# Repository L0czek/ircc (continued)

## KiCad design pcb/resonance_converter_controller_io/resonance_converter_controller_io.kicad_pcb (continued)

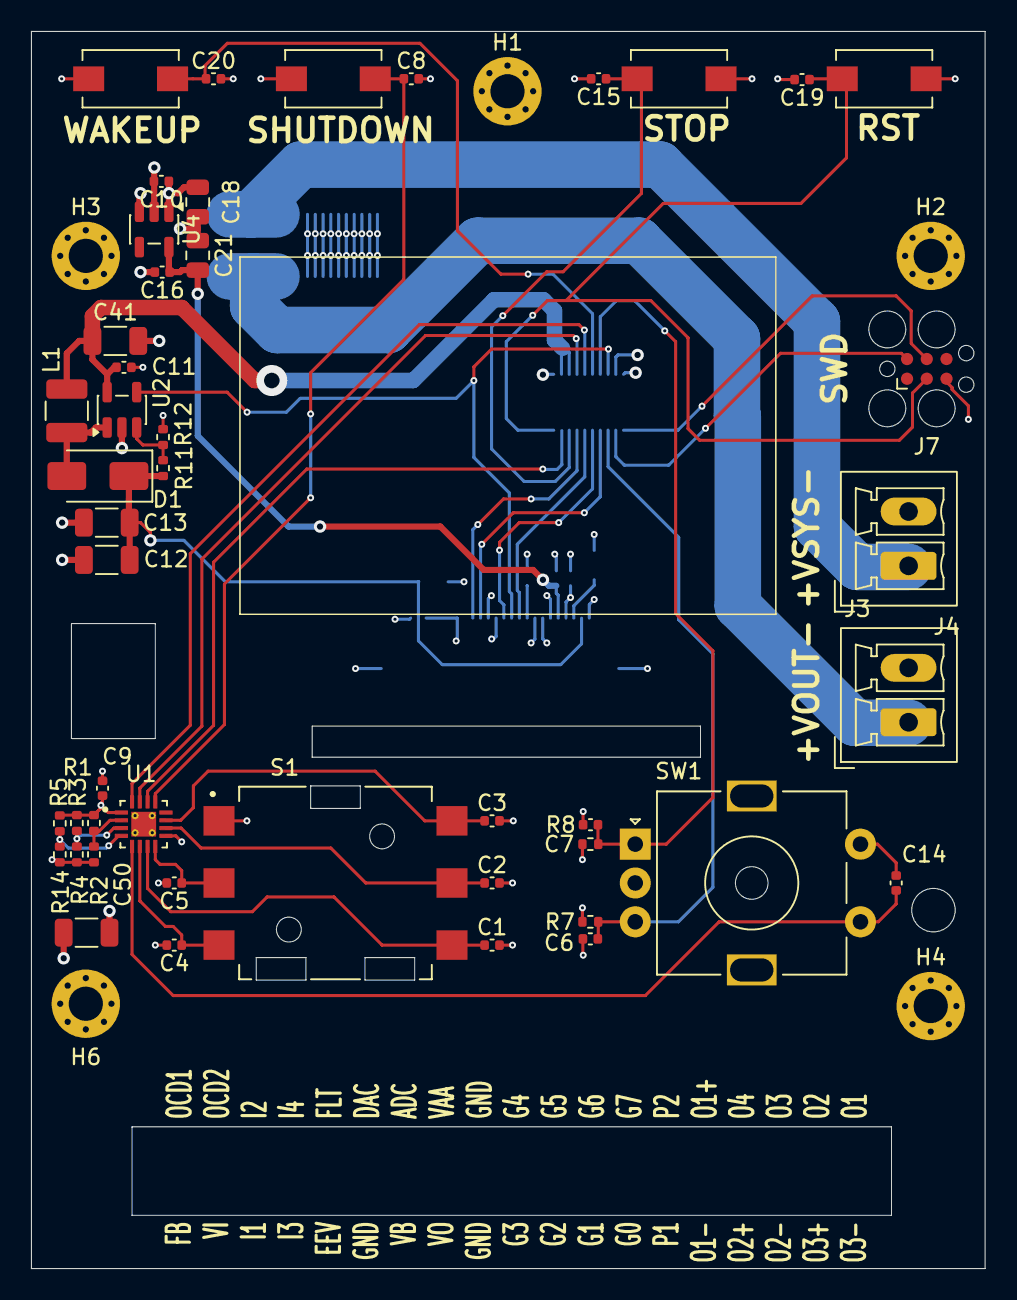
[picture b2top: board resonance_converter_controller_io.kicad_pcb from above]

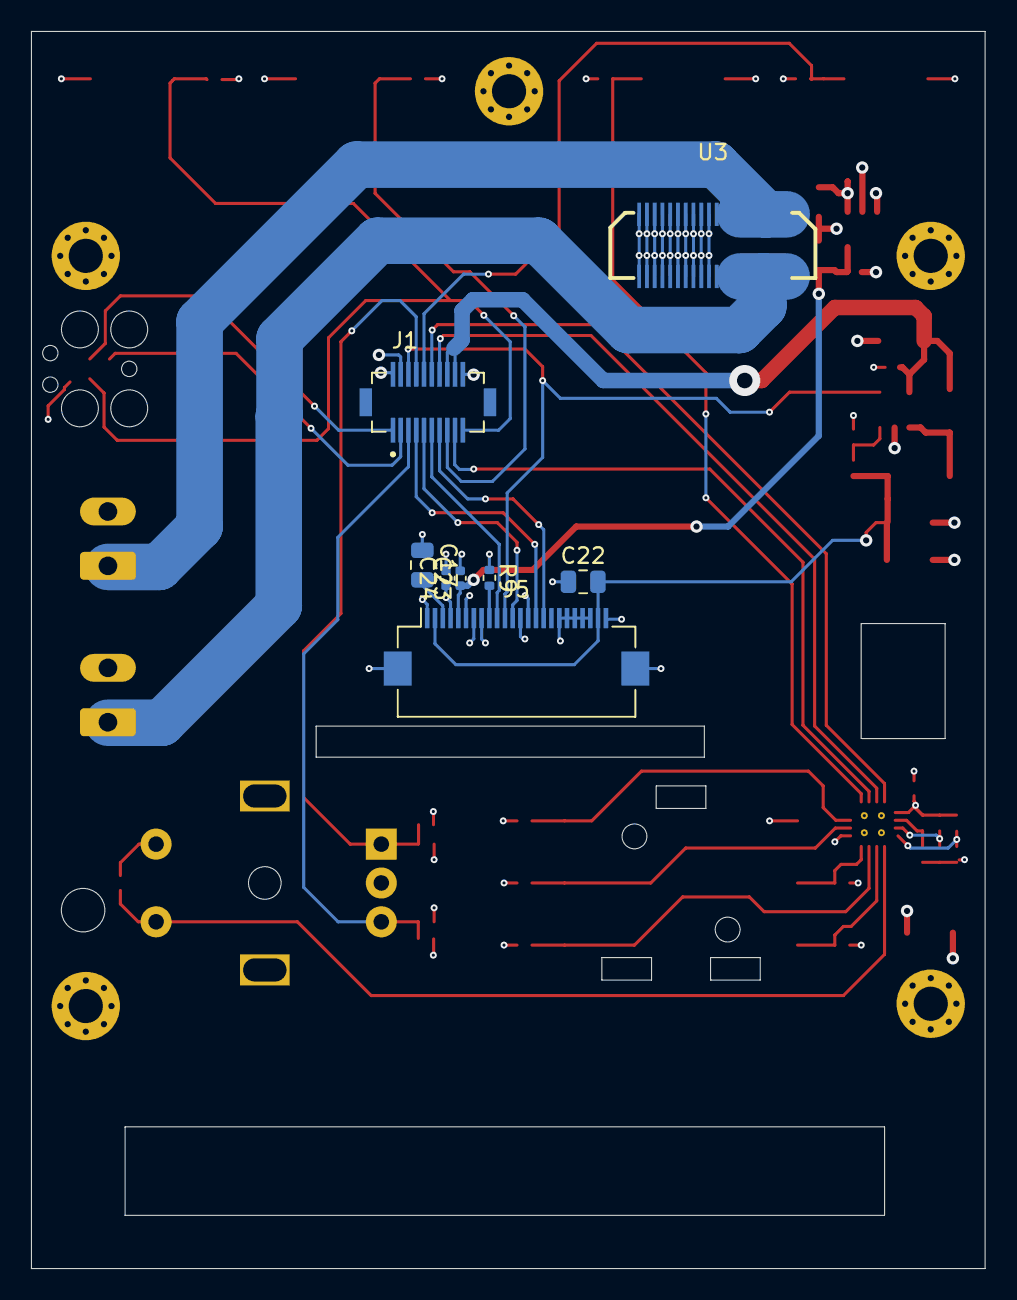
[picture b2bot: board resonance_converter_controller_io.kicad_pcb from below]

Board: 4 copper layers, 61.4 x 79.6 mm, 59 parts (8 on the bottom side), 36 nets.

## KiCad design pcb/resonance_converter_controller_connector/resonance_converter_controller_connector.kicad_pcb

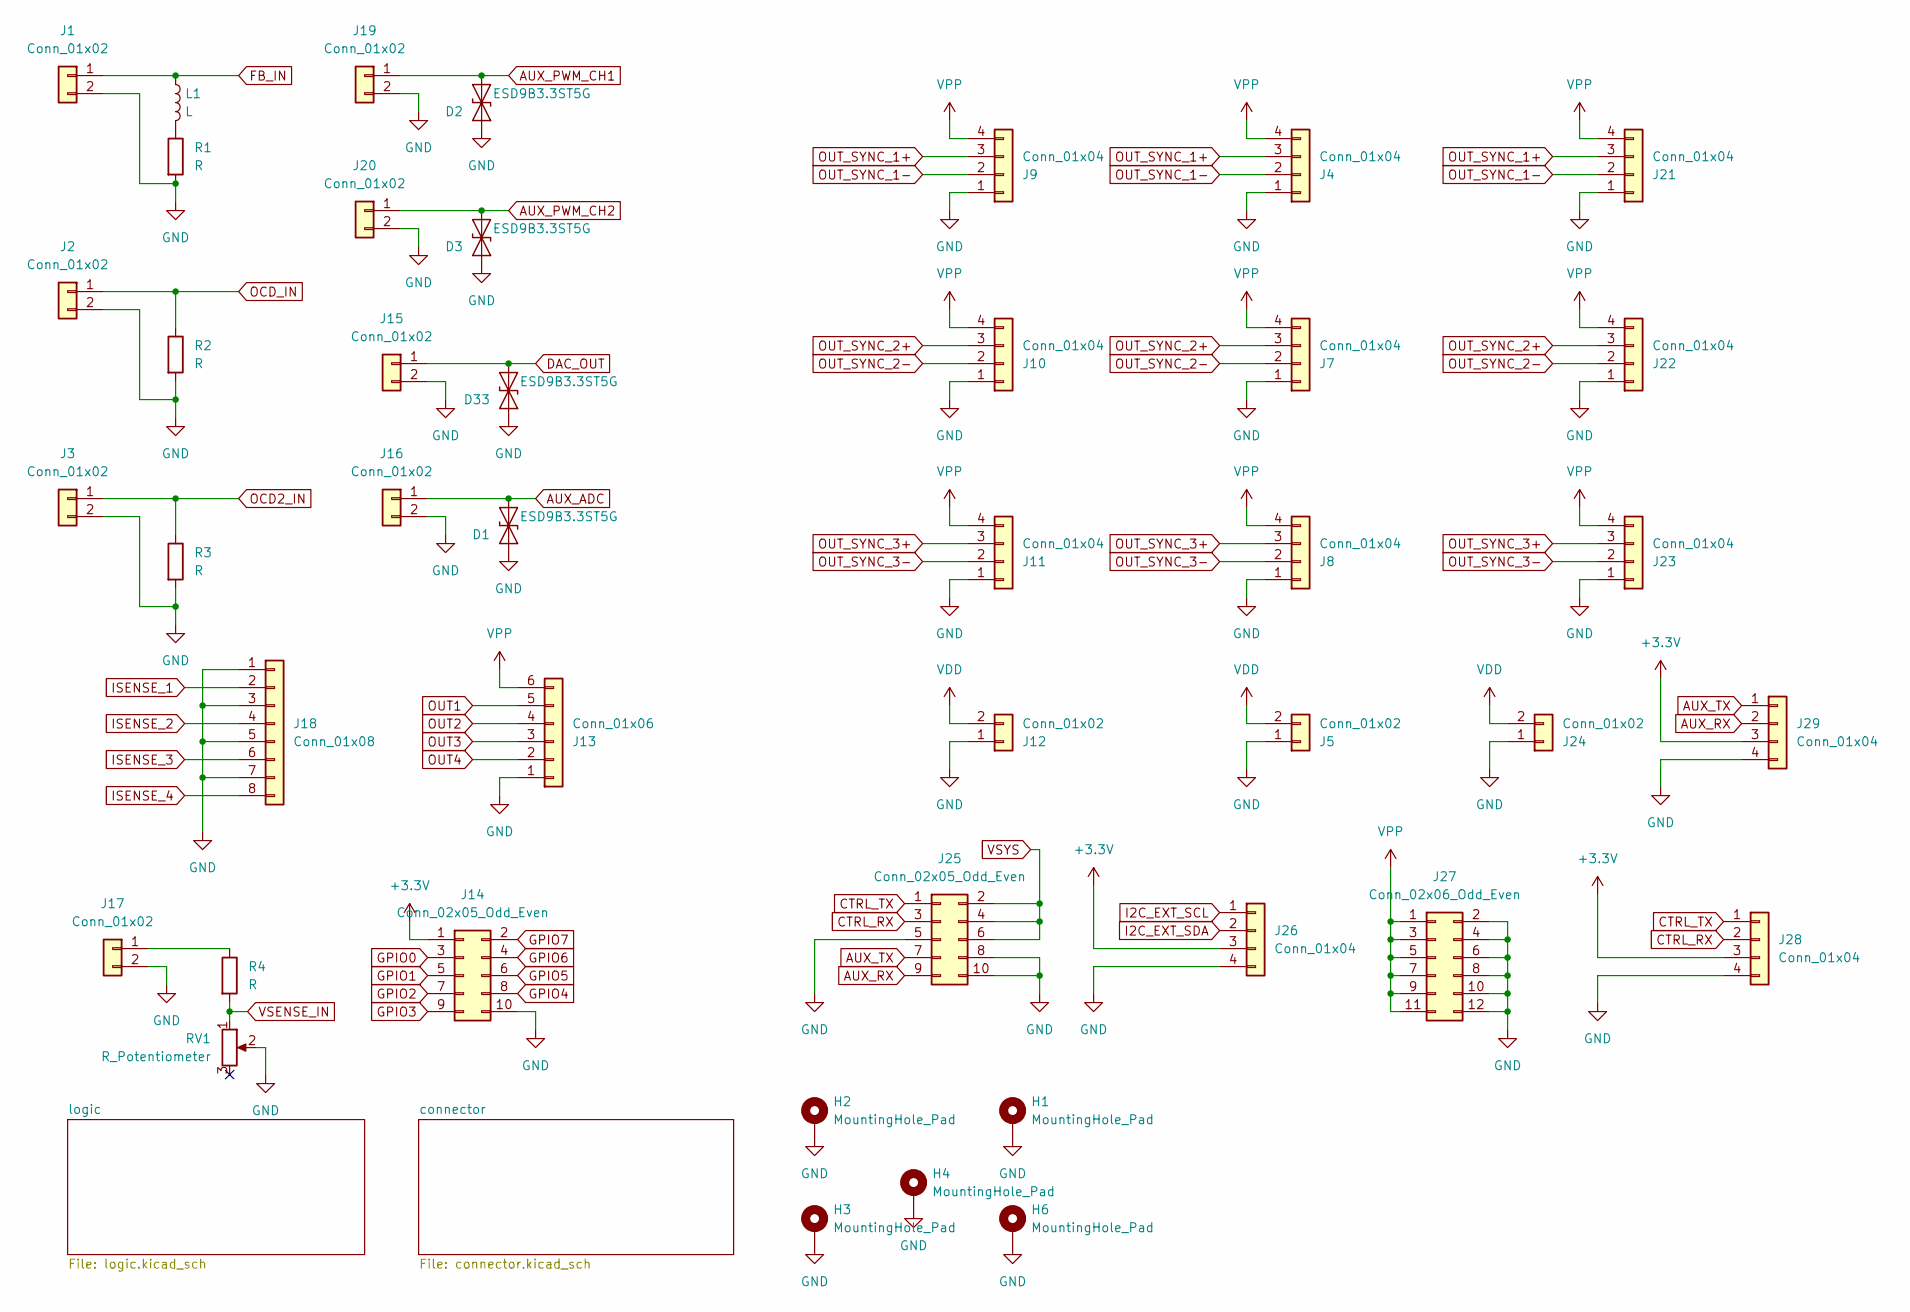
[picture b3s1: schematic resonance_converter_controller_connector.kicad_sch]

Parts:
D1, D2, D3, D33: ESD9B3.3ST5G; D_SOD-923
H1, H2, H3, H4, H6: MountingHole_Pad; MountingHole_2.2mm_M2_Pad_Via
J1, J2, J3, J15, J16, J17, J19, J20: Conn_01x02; PhoenixContact_MCV_1,5_2-G-5.08_1x02_P5.08mm_Vertical
J4, J7, J8, J9, J10, J11, J21, J22, J23, J26, J28, J29: Conn_01x04; JST_PH_B4B-PH-K_1x04_P2.00mm_Vertical
J5, J12, J24: Conn_01x02; AMASS_XT30U-M_1x02_P5.0mm_Vertical
J13: Conn_01x06; JST_PH_B6B-PH-K_1x06_P2.00mm_Vertical
J14, J25: Conn_02x05_Odd_Even; PinHeader_2x05_P2.54mm_Vertical
J18: Conn_01x08; PhoenixContact_MCV_1,5_8-G-3.5_1x08_P3.50mm_Vertical
J27: Conn_02x06_Odd_Even; PinHeader_2x06_P2.54mm_Vertical
L1: L; L_Radial_D12.0mm_P10.00mm_Neosid_SD12_style1
R1, R2, R3: R; TO-220-2_Vertical
R4: R; R_2010_5025Metric
RV1: R_Potentiometer; Potentiometer_Bourns_3269W_Vertical

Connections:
+3.3V: J14.1, J26.3, J28.3, J29.3; also elsewhere on the board
AUX_ADC: D1.1 (A1), J16.1; also elsewhere on the board
AUX_PWM_CH1: D2.1 (A1), J19.1; also elsewhere on the board
AUX_PWM_CH2: D3.1 (A1), J20.1; also elsewhere on the board
AUX_RX: J25.9, J29.2; also elsewhere on the board
AUX_TX: J25.7, J29.1; also elsewhere on the board
CTRL_RX: J25.3, J28.2; also elsewhere on the board
CTRL_TX: J25.1, J28.1; also elsewhere on the board
DAC_OUT: D33.1 (A1), J15.1; also elsewhere on the board
FB_IN: J1.1, L1.1; also elsewhere on the board
GND: D1.2 (A2), D2.2 (A2), D3.2 (A2), D33.2 (A2), H1.1 (1_1), H2.1 (1_1), H3.1 (1_1), H4.1 (1_1), H6.1 (1_1), J1.2, J2.2, J3.2, J4.1, J5.1, J7.1, J8.1, J9.1, J10.1, J11.1, J12.1, J13.1, J14.10, J15.2, J16.2, J17.2, J18.1, J18.3, J18.5, J18.7, J19.2, J20.2, J21.1, J22.1, J23.1, J24.1, J25.5, J25.8, J25.10, J26.4, J27.2, J27.4, J27.6, J27.8, J27.10, J27.12, J28.4, J29.4, R1.2, R2.2, R3.2, RV1.2; also elsewhere on the board
GPIO0: J14.3; also elsewhere on the board
GPIO1: J14.5; also elsewhere on the board
GPIO2: J14.7; also elsewhere on the board
GPIO3: J14.9; also elsewhere on the board
GPIO4: J14.8; also elsewhere on the board
GPIO5: J14.6; also elsewhere on the board
GPIO6: J14.4; also elsewhere on the board
GPIO7: J14.2; also elsewhere on the board
I2C_EXT_SCL: J26.1; also elsewhere on the board
I2C_EXT_SDA: J26.2; also elsewhere on the board
ISENSE_1: J18.2; also elsewhere on the board
ISENSE_2: J18.4; also elsewhere on the board
ISENSE_3: J18.6; also elsewhere on the board
ISENSE_4: J18.8; also elsewhere on the board
unnamed: J17.1, R4.1
unnamed: L1.2, R1.1
OCD2_IN: J3.1, R3.1; also elsewhere on the board
OCD_IN: J2.1, R2.1; also elsewhere on the board
OUT1: J13.5; also elsewhere on the board
OUT2: J13.4; also elsewhere on the board
OUT3: J13.3; also elsewhere on the board
OUT4: J13.2; also elsewhere on the board
OUT_SYNC_1+: J4.3, J9.3, J21.3; also elsewhere on the board
OUT_SYNC_1-: J4.2, J9.2, J21.2; also elsewhere on the board
OUT_SYNC_2+: J7.3, J10.3, J22.3; also elsewhere on the board
OUT_SYNC_2-: J7.2, J10.2, J22.2; also elsewhere on the board
OUT_SYNC_3+: J8.3, J11.3, J23.3; also elsewhere on the board
OUT_SYNC_3-: J8.2, J11.2, J23.2; also elsewhere on the board
VDD: J5.2, J12.2, J24.2; also elsewhere on the board
VPP: J4.4, J7.4, J8.4, J9.4, J10.4, J11.4, J13.6, J21.4, J22.4, J23.4, J27.1, J27.3, J27.5, J27.7, J27.9, J27.11; also elsewhere on the board
VSENSE_IN: R4.2, RV1.1; also elsewhere on the board
VSYS: J25.2, J25.4, J25.6; also elsewhere on the board

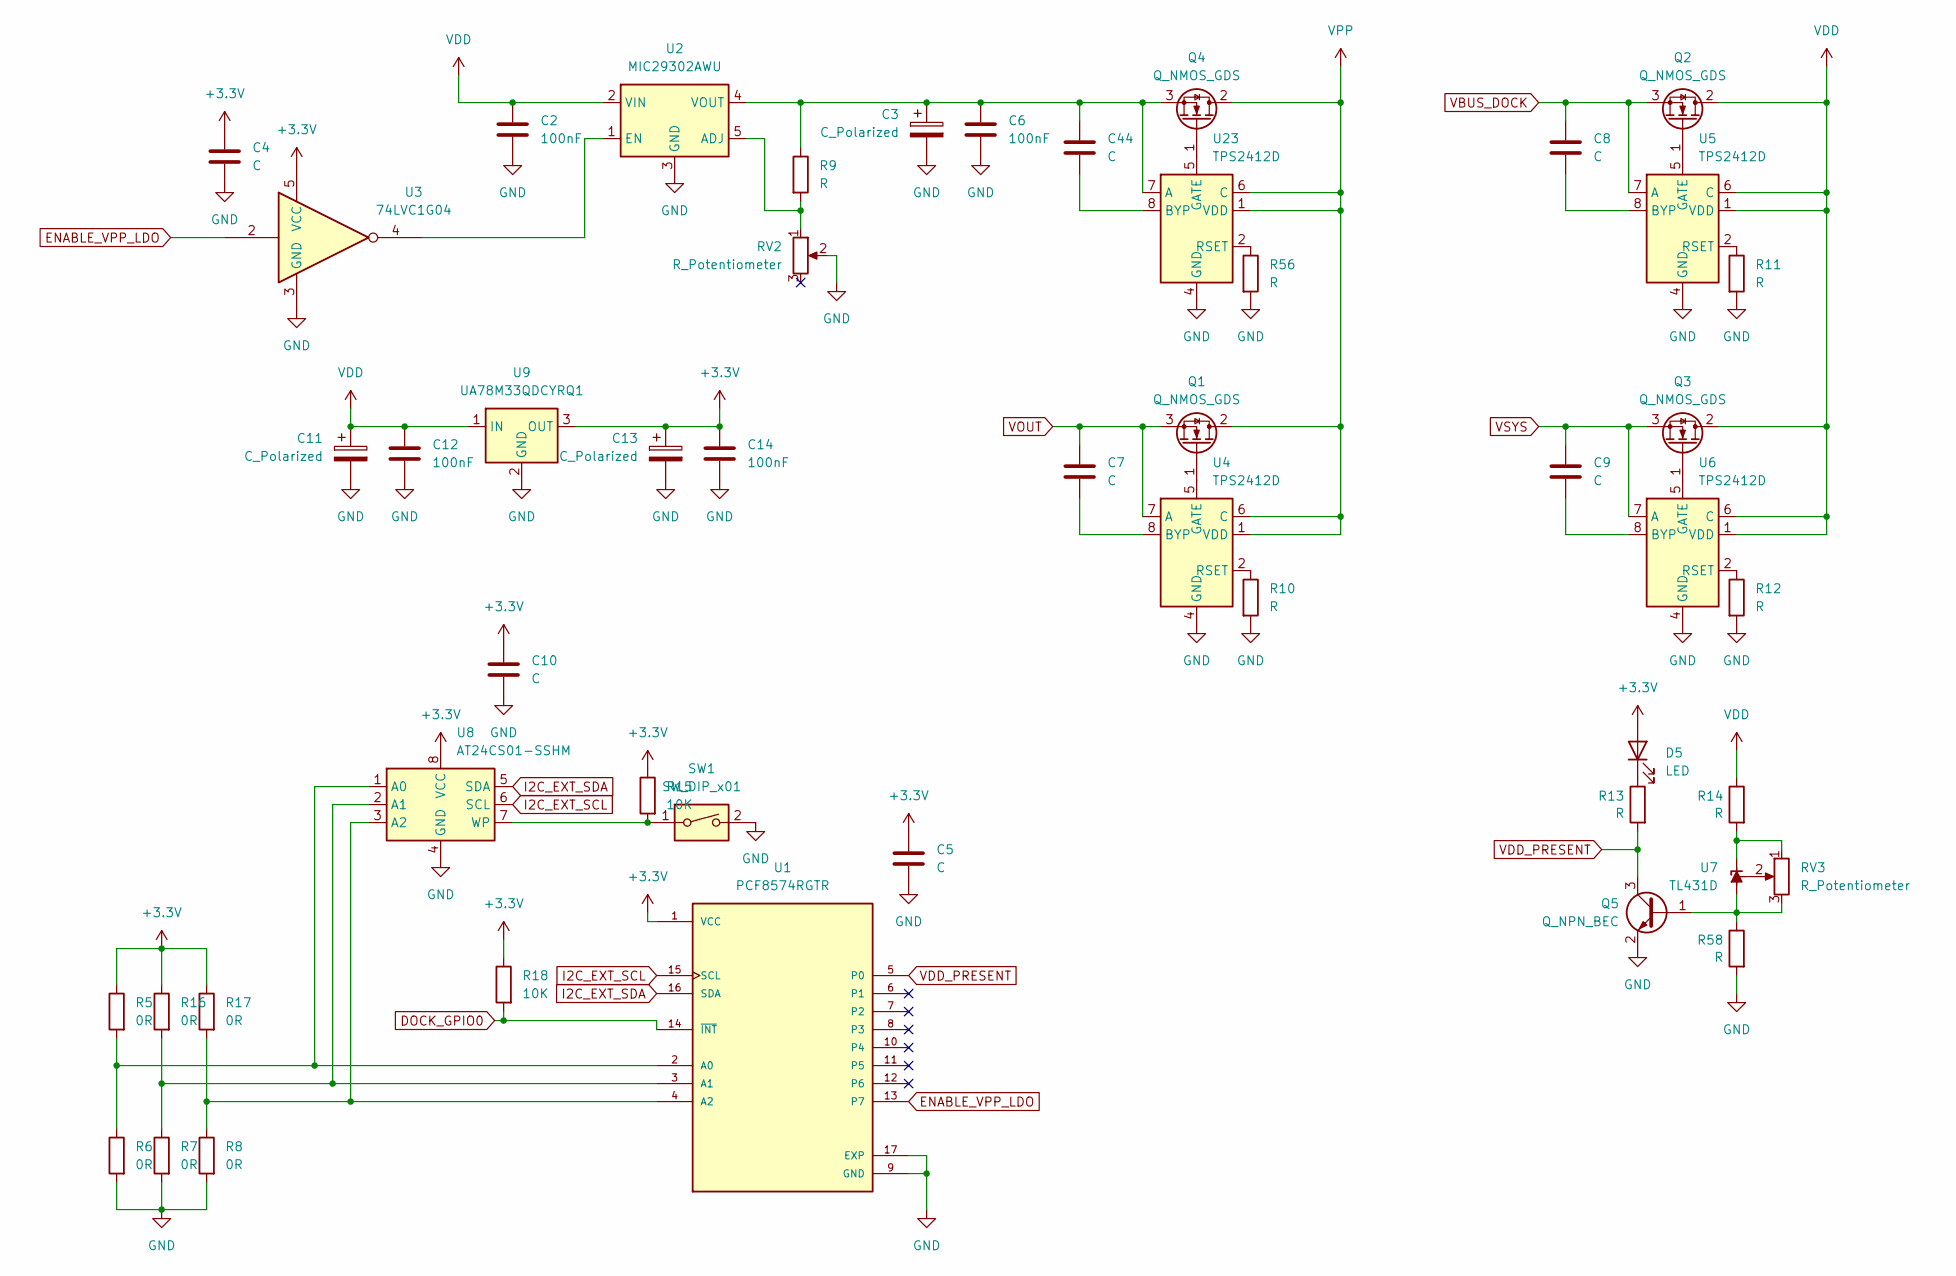
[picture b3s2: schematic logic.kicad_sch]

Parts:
C2, C6, C12, C14: 100nF; C_0402_1005Metric
C3, C11, C13: C_Polarized; CP_Elec_10x10
C4, C5, C7, C8, C9, C10, C44: C; C_0402_1005Metric
D5: LED; LED_1206_3216Metric
Q1, Q2, Q3, Q4: Q_NMOS_GDS; TO-252-2
Q5: Q_NPN_BEC; SOT-23
R5, R6, R7, R8, R16, R17: 0R; R_0402_1005Metric
R9, R10, R11, R12, R13, R14, R56, R58: R; R_0402_1005Metric
R15, R18: 10K; R_0402_1005Metric
RV2, RV3: R_Potentiometer; Potentiometer_Bourns_3269W_Vertical
SW1: SW_DIP_x01; SW_DIP_SPSTx01_Slide_9.78x4.72mm_W8.61mm_P2.54mm
U1: PCF8574RGTR; QFN50P300X300X100-17N; PARTREV J; DigiKey_Part_Number 296-21238-1-ND
U2: MIC29302AWU; TO-263-5_TabPin3
U3: 74LVC1G04; SOT-23-5
U4, U5, U6, U23: TPS2412D; TSSOP-8_4.4x3mm_P0.65mm
U7: TL431D; SOIC-8_3.9x4.9mm_P1.27mm
U8: AT24CS01-SSHM; SOIC-8_3.9x4.9mm_P1.27mm
U9: UA78M33QDCYRQ1; SOT-223-3_TabPin2

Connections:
+3.3V: C4.1, C5.1, C10.1, C13.1, C14.1, D5.2 (A), R5.1, R15.1, R16.1, R17.1, R18.1, U1.1 (VCC), U3.5 (VCC), U8.8 (VCC), U9.3 (OUT); also elsewhere on the board
DOCK_GPIO0: R18.2, U1.14 (~INT)
ENABLE_VPP_LDO: U1.13 (P7), U3.2
GND: C2.2, C3.2, C4.2, C5.2, C6.2, C10.2, C11.2, C12.2, C13.2, C14.2, Q5.2 (E), R6.2, R7.2, R8.2, R10.2, R11.2, R12.2, R56.2, R58.2, RV2.2, SW1.2, U1.9 (GND), U1.17 (EXP), U2.3 (GND), U3.3 (GND), U4.3 (GND), U4.4 (GND), U5.3 (GND), U5.4 (GND), U6.3 (GND), U6.4 (GND), U8.4 (GND), U9.2 (GND), U23.3 (GND), U23.4 (GND); also elsewhere on the board
I2C_EXT_SCL: U1.15 (SCL), U8.6 (SCL); also elsewhere on the board
I2C_EXT_SDA: U1.16 (SDA), U8.5 (SDA); also elsewhere on the board
unnamed: D5.1 (K), R13.1
unnamed: Q1.1 (G), U4.5 (GATE)
unnamed: Q2.1 (G), U5.5 (GATE)
unnamed: Q3.1 (G), U6.5 (GATE)
unnamed: Q4.1 (G), U23.5 (GATE)
unnamed: C3.1, C6.1, C44.1, Q4.3 (S), R9.1, U2.4 (VOUT), U23.7 (A)
unnamed: Q5.1 (B), R58.1, RV3.3, U7.2 (A), U7.3 (A), U7.6 (A), U7.7 (A)
unnamed: R5.2, R6.1, U1.2 (A0), U8.1 (A0)
unnamed: R7.1, R16.2, U1.3 (A1), U8.2 (A1)
unnamed: R8.1, R17.2, U1.4 (A2), U8.3 (A2)
unnamed: R9.2, RV2.1, U2.5 (ADJ)
unnamed: U2.1 (EN), U3.4
unnamed: C7.2, U4.8 (BYP)
unnamed: R10.1, U4.2 (RSET)
unnamed: C8.2, U5.8 (BYP)
unnamed: R11.1, U5.2 (RSET)
unnamed: C9.2, U6.8 (BYP)
unnamed: R12.1, U6.2 (RSET)
unnamed: R14.2, RV3.1, U7.1 (K)
unnamed: RV3.2, U7.8 (REF)
unnamed: R15.2, SW1.1, U8.7 (WP)
unnamed: C44.2, U23.8 (BYP)
unnamed: R56.1, U23.2 (RSET)
VBUS_DOCK: C8.1, Q2.3 (S), U5.7 (A); also elsewhere on the board
VDD: C2.1, C11.1, C12.1, Q2.2 (D), Q3.2 (D), R14.1, U2.2 (VIN), U5.1 (VDD), U5.6 (C), U6.1 (VDD), U6.6 (C), U9.1 (IN); also elsewhere on the board
VDD_PRESENT: Q5.3 (C), R13.2, U1.5 (P0)
VOUT: C7.1, Q1.3 (S), U4.7 (A); also elsewhere on the board
VPP: Q1.2 (D), Q4.2 (D), U4.1 (VDD), U4.6 (C), U23.1 (VDD), U23.6 (C); also elsewhere on the board
VSYS: C9.1, Q3.3 (S), U6.7 (A); also elsewhere on the board

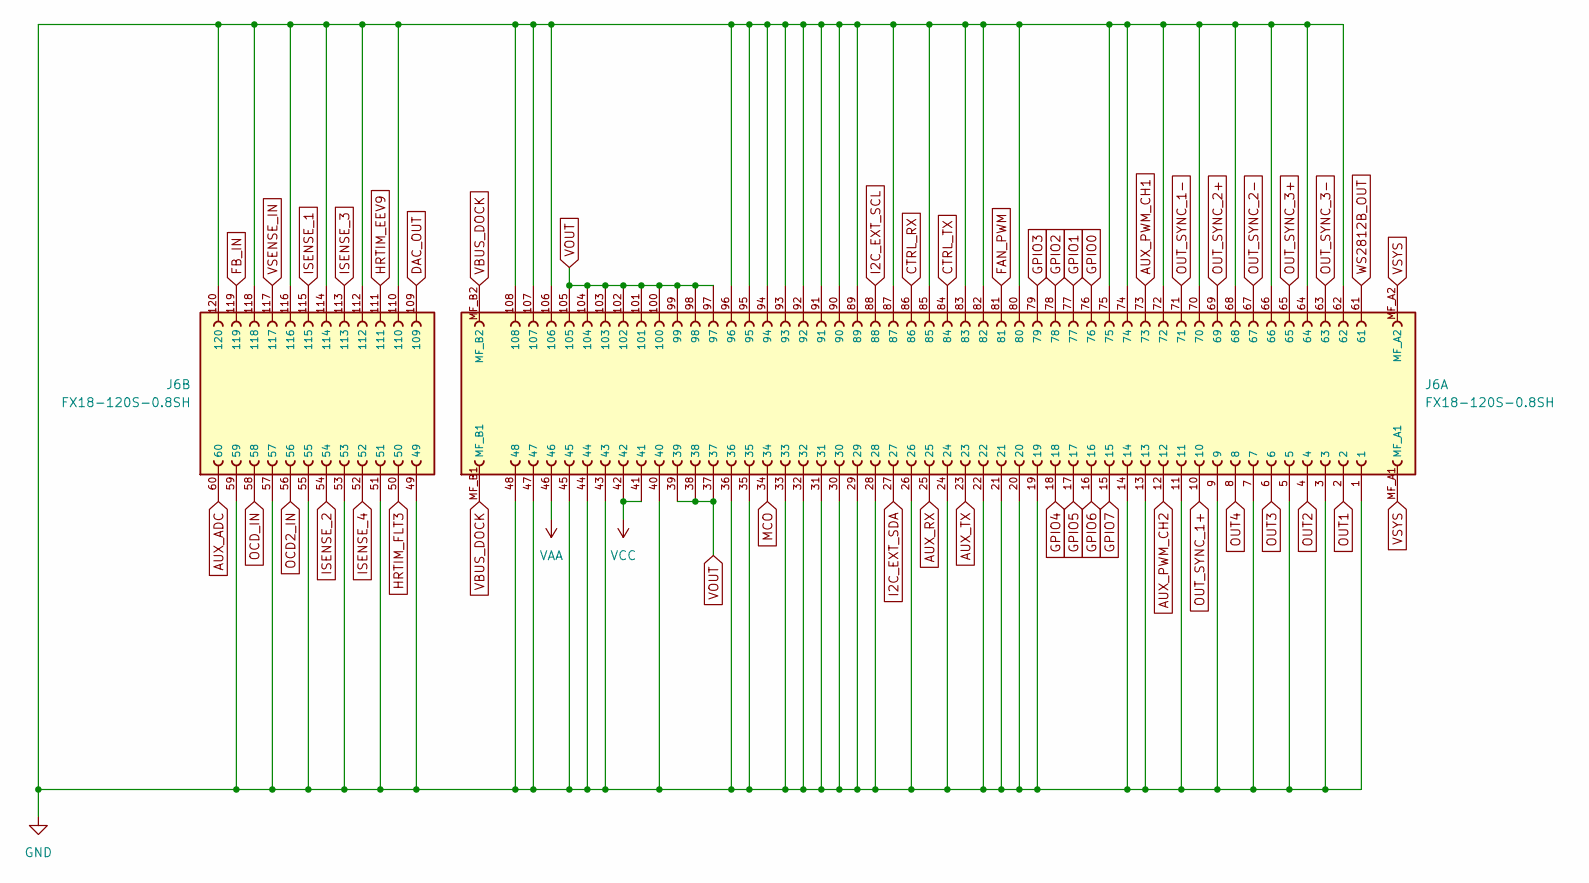
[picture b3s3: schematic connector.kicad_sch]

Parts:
J6: FX18-120S-0.8SH; HIROSE_FX18-120S-0.8SH; PARTREV 1

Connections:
AUX_ADC: J6.60; also elsewhere on the board
AUX_PWM_CH1: J6.73; also elsewhere on the board
AUX_PWM_CH2: J6.12; also elsewhere on the board
AUX_RX: J6.25; also elsewhere on the board
AUX_TX: J6.23; also elsewhere on the board
CTRL_RX: J6.86; also elsewhere on the board
CTRL_TX: J6.84; also elsewhere on the board
DAC_OUT: J6.109; also elsewhere on the board
FAN_PWM: J6.81
FB_IN: J6.119; also elsewhere on the board
GND: J6.1, J6.3, J6.5, J6.7, J6.9, J6.11, J6.13, J6.14, J6.19, J6.20, J6.21, J6.22, J6.24, J6.26, J6.28, J6.29, J6.30, J6.31, J6.32, J6.33, J6.35, J6.36, J6.40, J6.43, J6.44, J6.45, J6.47, J6.48, J6.49, J6.51, J6.53, J6.55, J6.57, J6.59, J6.62, J6.64, J6.66, J6.68, J6.70, J6.72, J6.74, J6.75, J6.80, J6.82, J6.83, J6.85, J6.87, J6.89, J6.90, J6.91, J6.92, J6.93, J6.94, J6.95, J6.96, J6.106, J6.107, J6.108, J6.110, J6.112, J6.114, J6.116, J6.118, J6.120; also elsewhere on the board
GPIO0: J6.76; also elsewhere on the board
GPIO1: J6.77; also elsewhere on the board
GPIO2: J6.78; also elsewhere on the board
GPIO3: J6.79; also elsewhere on the board
GPIO4: J6.18; also elsewhere on the board
GPIO5: J6.17; also elsewhere on the board
GPIO6: J6.16; also elsewhere on the board
GPIO7: J6.15; also elsewhere on the board
HRTIM_EEV9: J6.111
HRTIM_FLT3: J6.50
I2C_EXT_SCL: J6.88; also elsewhere on the board
I2C_EXT_SDA: J6.27; also elsewhere on the board
ISENSE_1: J6.115; also elsewhere on the board
ISENSE_2: J6.54; also elsewhere on the board
ISENSE_3: J6.113; also elsewhere on the board
ISENSE_4: J6.52; also elsewhere on the board
MCO: J6.34
OCD2_IN: J6.56; also elsewhere on the board
OCD_IN: J6.58; also elsewhere on the board
OUT1: J6.2; also elsewhere on the board
OUT2: J6.4; also elsewhere on the board
OUT3: J6.6; also elsewhere on the board
OUT4: J6.8; also elsewhere on the board
OUT_SYNC_1+: J6.10; also elsewhere on the board
OUT_SYNC_1-: J6.71; also elsewhere on the board
OUT_SYNC_2+: J6.69; also elsewhere on the board
OUT_SYNC_2-: J6.67; also elsewhere on the board
OUT_SYNC_3+: J6.65; also elsewhere on the board
OUT_SYNC_3-: J6.63; also elsewhere on the board
VAA: J6.46
VBUS_DOCK: J6.MF_B1, J6.MF_B2; also elsewhere on the board
VCC: J6.41, J6.42
VOUT: J6.37, J6.38, J6.39, J6.97, J6.98, J6.99, J6.100, J6.101, J6.102, J6.103, J6.104, J6.105; also elsewhere on the board
VSENSE_IN: J6.117; also elsewhere on the board
VSYS: J6.MF_A1, J6.MF_A2; also elsewhere on the board
WS2812B_OUT: J6.61

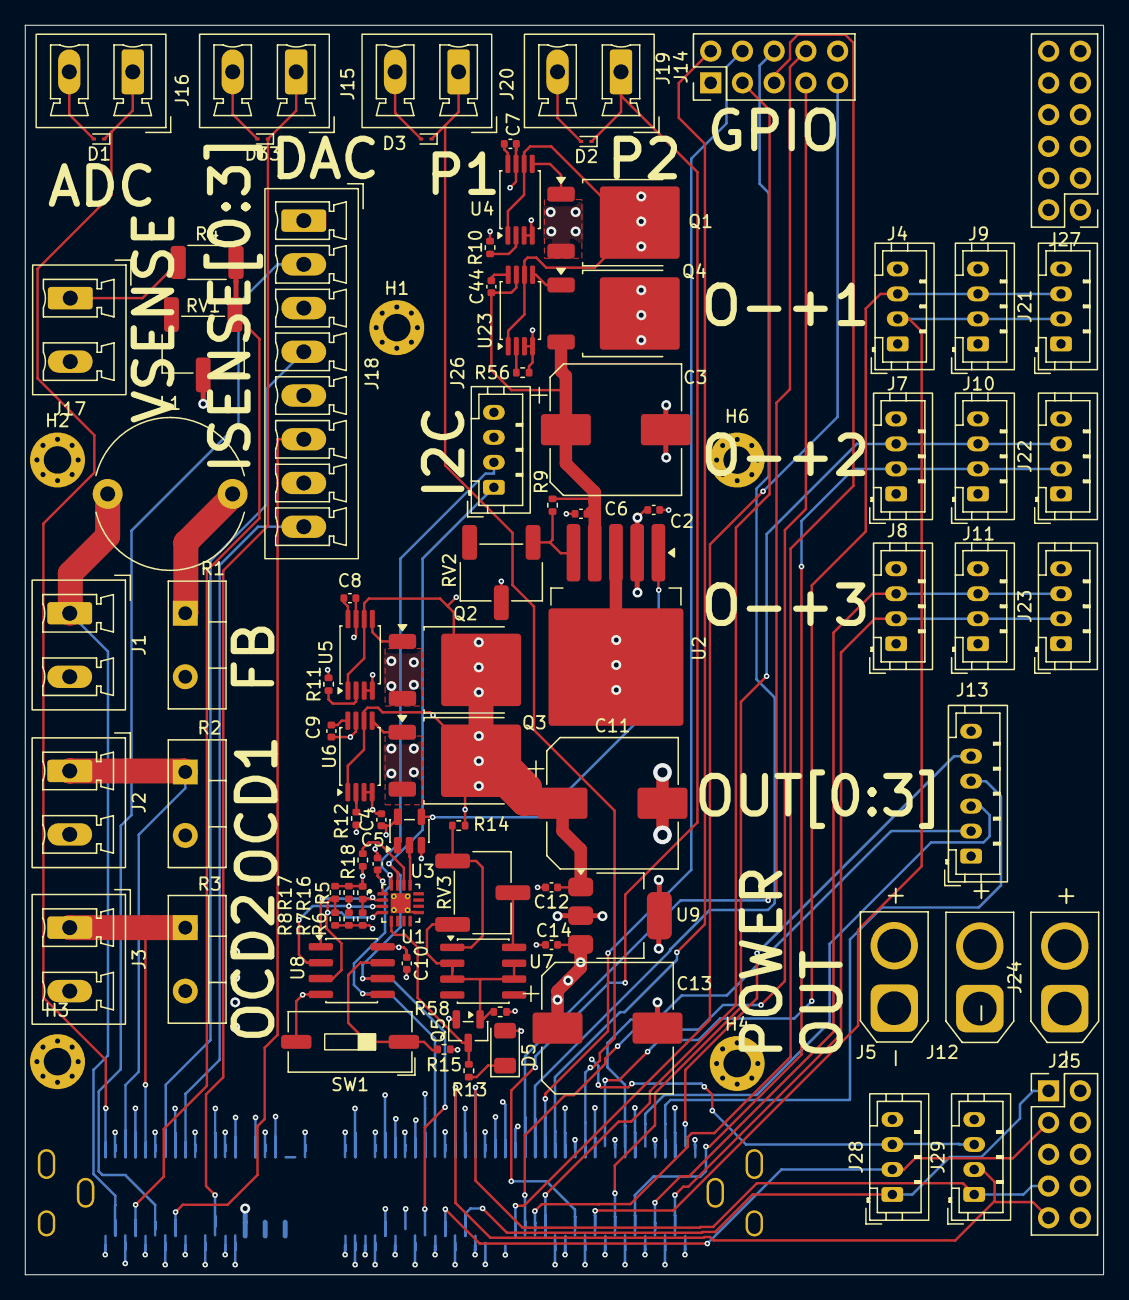
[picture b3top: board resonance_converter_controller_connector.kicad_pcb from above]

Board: 4 copper layers, 86.3 x 100.0 mm, 93 parts (1 on the bottom side), 72 nets.

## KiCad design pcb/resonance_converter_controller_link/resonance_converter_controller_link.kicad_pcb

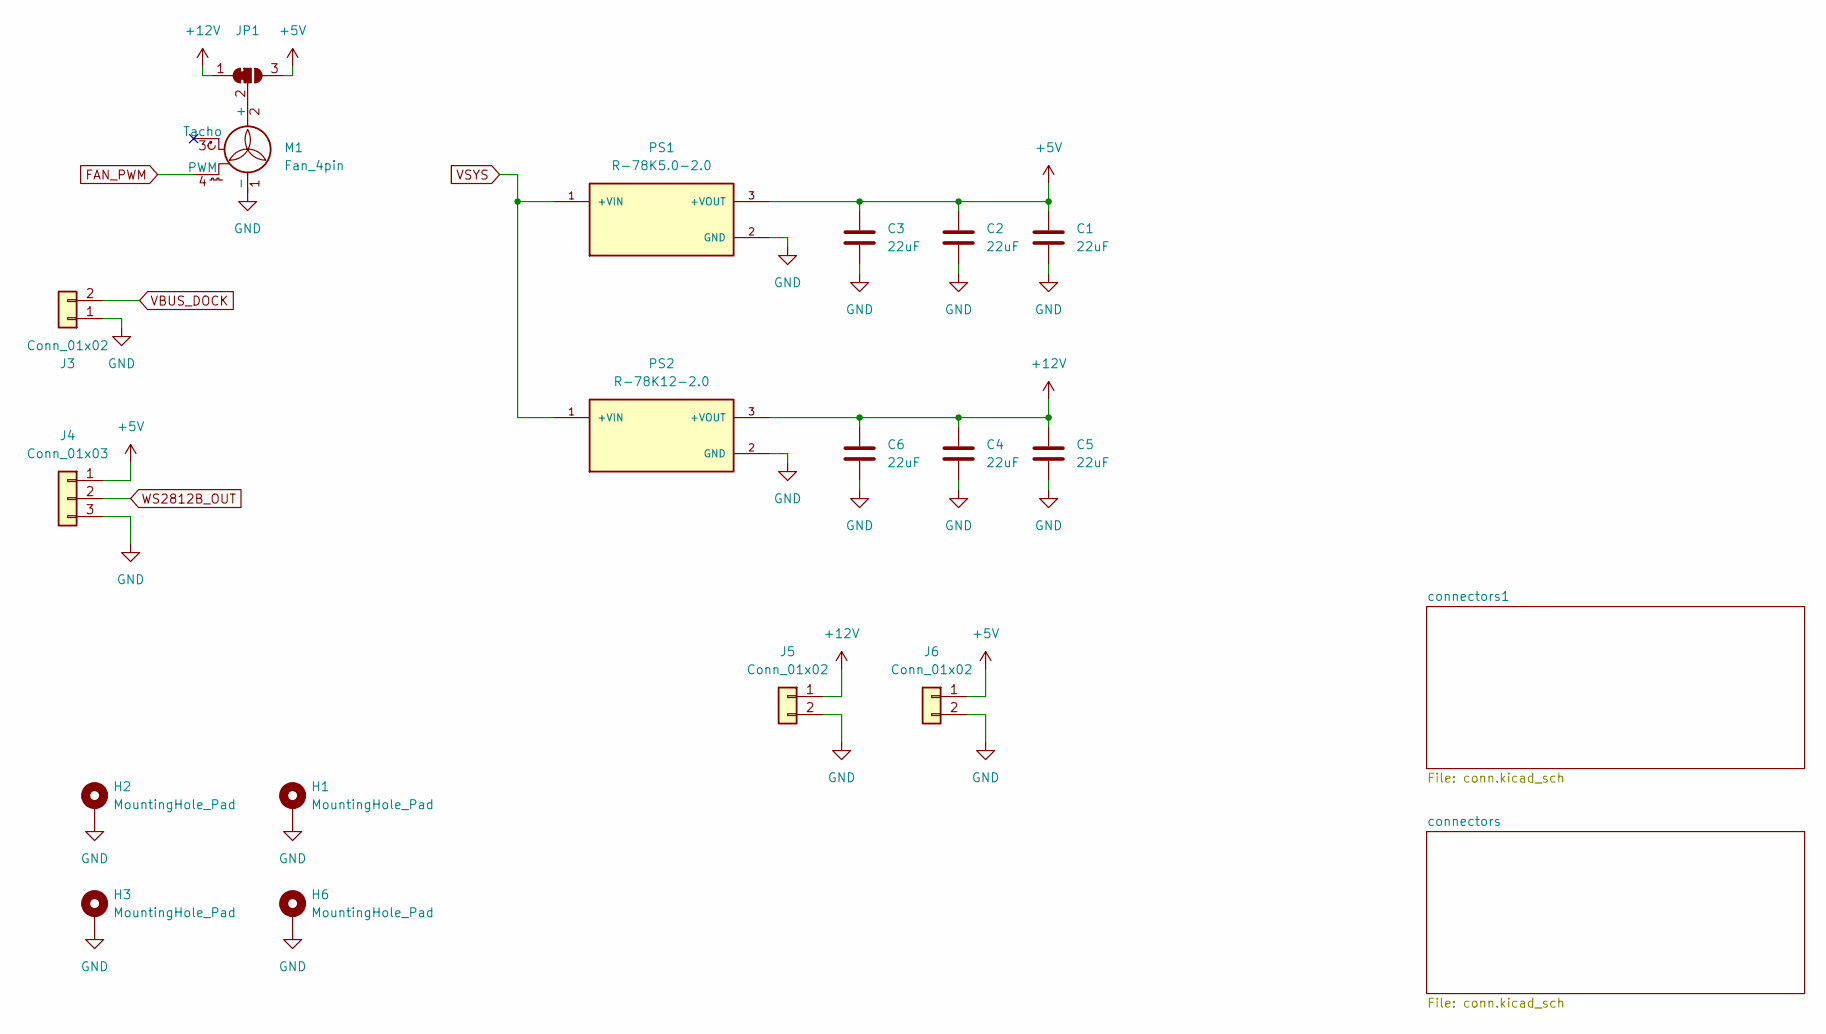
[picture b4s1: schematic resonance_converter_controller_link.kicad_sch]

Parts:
C1, C2, C3, C4, C5, C6: 22uF; C_1206_3216Metric
H1, H2, H3, H6: MountingHole_Pad; MountingHole_2.2mm_M2_Pad_Via
J3: Conn_01x02; PhoenixContact_MC_1,5_2-GF-5.08_1x02_P5.08mm_Horizontal_Thr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
J4: Conn_01x03; PinHeader_1x03_P2.54mm_Horizontal
J5, J6: Conn_01x02; PhoenixContact_MC_1,5_2-G-5.08_1x02_P5.08mm_Horizontal
JP1: SolderJumper_3_Bridged12; SolderJumper-3_P1.3mm_Bridged12_RoundedPad1.0x1.5mm
M1: Fan_4pin; FanPinHeader_1x04_P2.54mm_Vertical
PS1: R-78K5.0-2.0; CONV_R-78K5.0-2.0; MPN R-78K5.0-2.0
PS2: R-78K12-2.0; CONV_R-78K12-2.0; MPN R-78K12-2.0

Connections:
+5V: C1.1, C2.1, C3.1, J4.1, J6.1, JP1.3 (B), PS1.3 (+VOUT)
+12V: C4.1, C5.1, C6.1, J5.1, JP1.1 (A), PS2.3 (+VOUT)
FAN_PWM: M1.4 (PWM); also elsewhere on the board
GND: C1.2, C2.2, C3.2, C4.2, C5.2, C6.2, H1.1 (1_1), H2.1 (1_1), H3.1 (1_1), H6.1 (1_1), J3.1, J4.3, J5.2, J6.2, M1.1 (-), PS1.2 (GND), PS2.2 (GND); also elsewhere on the board
unnamed: JP1.2 (C), M1.2 (+)
VBUS_DOCK: J3.2; also elsewhere on the board
VSYS: PS1.1 (+VIN), PS2.1 (+VIN); also elsewhere on the board
WS2812B_OUT: J4.2; also elsewhere on the board
